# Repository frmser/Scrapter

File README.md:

# Scrapter
Scrapter is a trash sorting robot

This project was done during the Hackathon Slash 2022

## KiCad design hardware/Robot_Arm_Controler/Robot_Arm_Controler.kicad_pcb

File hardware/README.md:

# scrapterhardware

## printedparts

This folder will contain the stl files for 3D printed parts

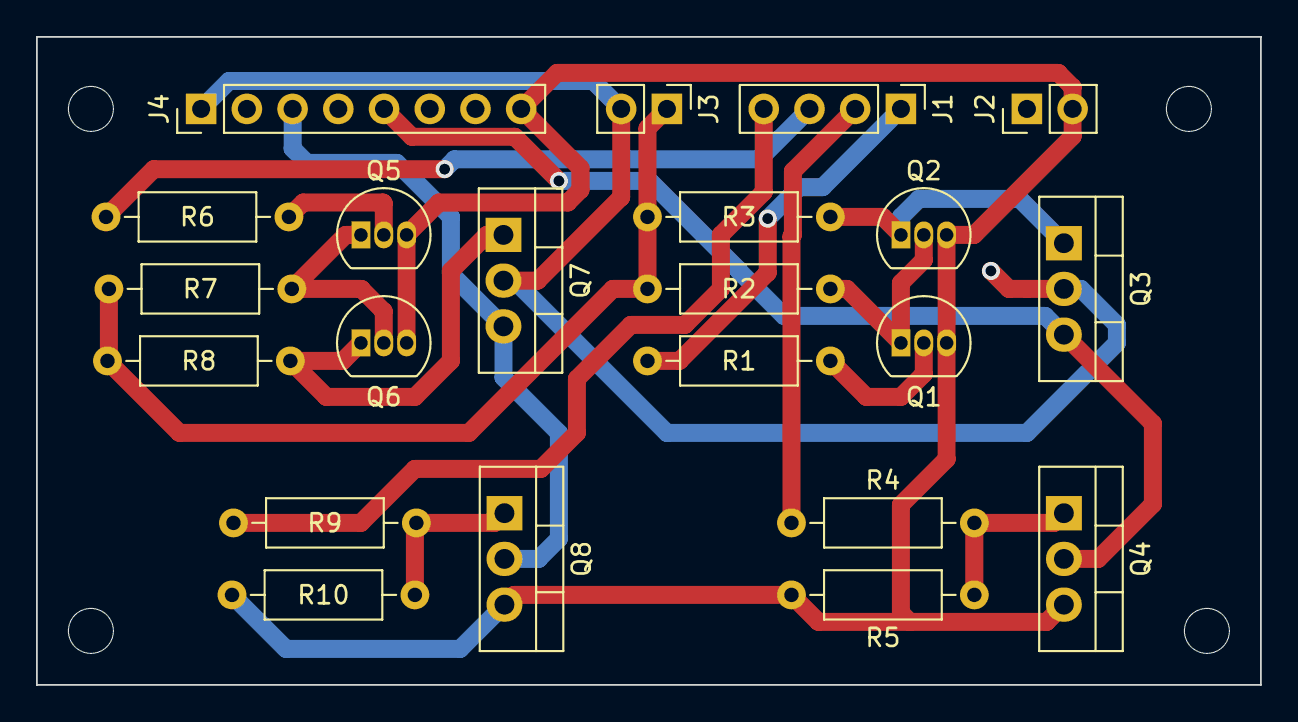
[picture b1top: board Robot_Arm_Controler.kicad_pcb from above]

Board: 2 copper layers, 68.0 x 36.0 mm, 26 parts (0 on the bottom side), 17 nets.

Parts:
H1, H2, H3, H4: MountingHole; MountingHole_2.5mm
J1: ESP_Control_Signals; PinHeader_1x04_P2.54mm_Vertical
J2: ESP_32_Supply; PinHeader_1x02_P2.54mm_Vertical
J3: Isolated Auxiliary Supply; PinHeader_1x02_P2.54mm_Vertical
J4: Robot Arm Connector; PinHeader_1x08_P2.54mm_Vertical
Q1, Q2, Q5, Q6: 2N2222; TO-92_Inline
Q3, Q7: IRF540N; TO-220-3_Vertical
Q4, Q8: IRZ44; TO-220-3_Vertical
R1, R2, R3, R4, R6, R7, R8, R9: 680; R_Axial_DIN0207_L6.3mm_D2.5mm_P10.16mm_Horizontal
R5, R10: 68k; R_Axial_DIN0207_L6.3mm_D2.5mm_P10.16mm_Horizontal

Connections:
/Channel_1_Down: J1.2, R4.1
/Channel_1_Up: J1.1, R1.1
/Channel_2_Down: J1.4, R9.1
/Channel_2_Up: J1.3, R6.1
/Positive_Arm: J3.2, J4.1, Q3.2 (D), Q7.2 (D)
/Rotation_Axis: J4.3, Q7.3 (S), Q8.2 (D)
/Vertical_Axis: J4.5, Q3.3 (S), Q4.2 (D)
GND: J2.2, J4.8, Q1.3 (E), Q2.3 (E), Q4.3 (S), Q5.3 (E), Q6.3 (E), Q8.3 (S), R5.2, R10.2
unnamed: Q1.1 (C), Q2.2 (B), R2.2
unnamed: Q1.2 (B), R1.2
unnamed: Q2.1 (C), Q3.1 (G), R3.2
unnamed: Q4.1 (G), R4.2, R5.1
unnamed: Q5.1 (C), Q6.2 (B), R7.2
unnamed: Q5.2 (B), R6.2
unnamed: Q6.1 (C), Q7.1 (G), R8.2
unnamed: Q8.1 (G), R9.2, R10.1
VDD: J3.1, R2.1, R3.1, R7.1, R8.1

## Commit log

2022-09-25 Apparently works-for-me is a crappy excuse.
